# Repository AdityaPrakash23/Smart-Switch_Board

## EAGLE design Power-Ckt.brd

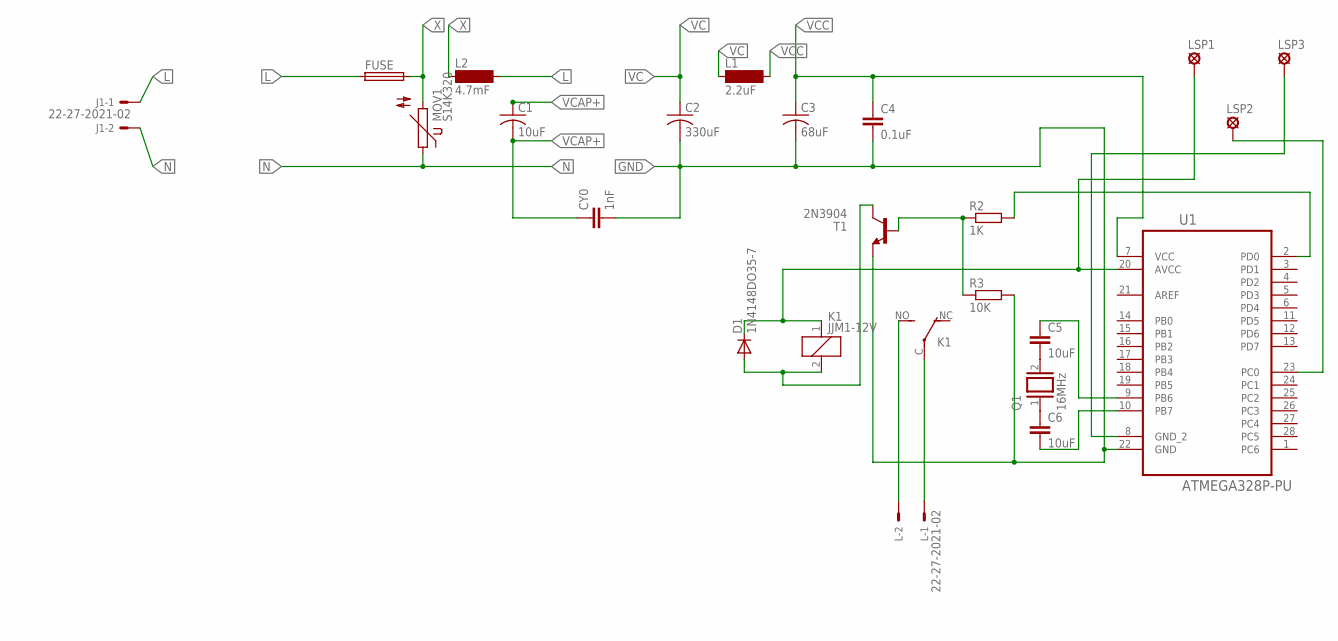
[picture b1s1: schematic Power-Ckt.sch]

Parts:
C1: 10uF; C0805K
C2: 330uF; C0805K
C3: 68uF; C0805K
C4: 0.1uF; C1808
C5, C6: 10uF; C2.5-3
CY0: 1nF; C1808
D1: 1N4148DO35-7; DO35-7
FUSE: GSH15
J1: 22-27-2021-02; 6410-02
K1: JJM1-12V; JJM1C
L: 22-27-2021-02; 6410-02
L1: 2.2uF; SM-1206
L2: 4.7mF; SM-1206
LSP1, LSP2, LSP3: LSP13
MOV1: S14K320
Q1: 16MHz; QS
R2: 1K; 0204/5
R3: 10K; 0204/5
T1: 2N3904; TO92
U1: ATMEGA328P-PU; DIP254P762X457-28

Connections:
GND: C2.2, C3.2, C4.2, CY0.2, R3.2, T1.3 (E), U1.22 (GND)
L: FUSE.1, J1.1, L2.2
N: J1.2, MOV1.1
unnamed: R2.2, U1.2 (PD0)
unnamed: C5.2, Q1.2
unnamed: C6.1, Q1.1
unnamed: C5.1, U1.9 (PB6)
unnamed: C6.2, U1.10 (PB7)
unnamed: LSP2.MP, U1.23 (PC0)
unnamed: D1.C, K1.1, LSP1.MP, U1.20 (AVCC)
unnamed: LSP3.MP, U1.8 (GND_2)
unnamed: K1.NO (S), L.2
unnamed: K1.C, L.1
unnamed: R2.1, R3.1, T1.2 (B)
unnamed: D1.A, K1.2, T1.1 (C)
VC: C2.1, L1.1
VCAP+: C1.1
VCAP-: C1.2, CY0.1
VCC: C3.1, C4.1, L1.2, U1.7 (VCC)
X: FUSE.2, L2.1, MOV1.2

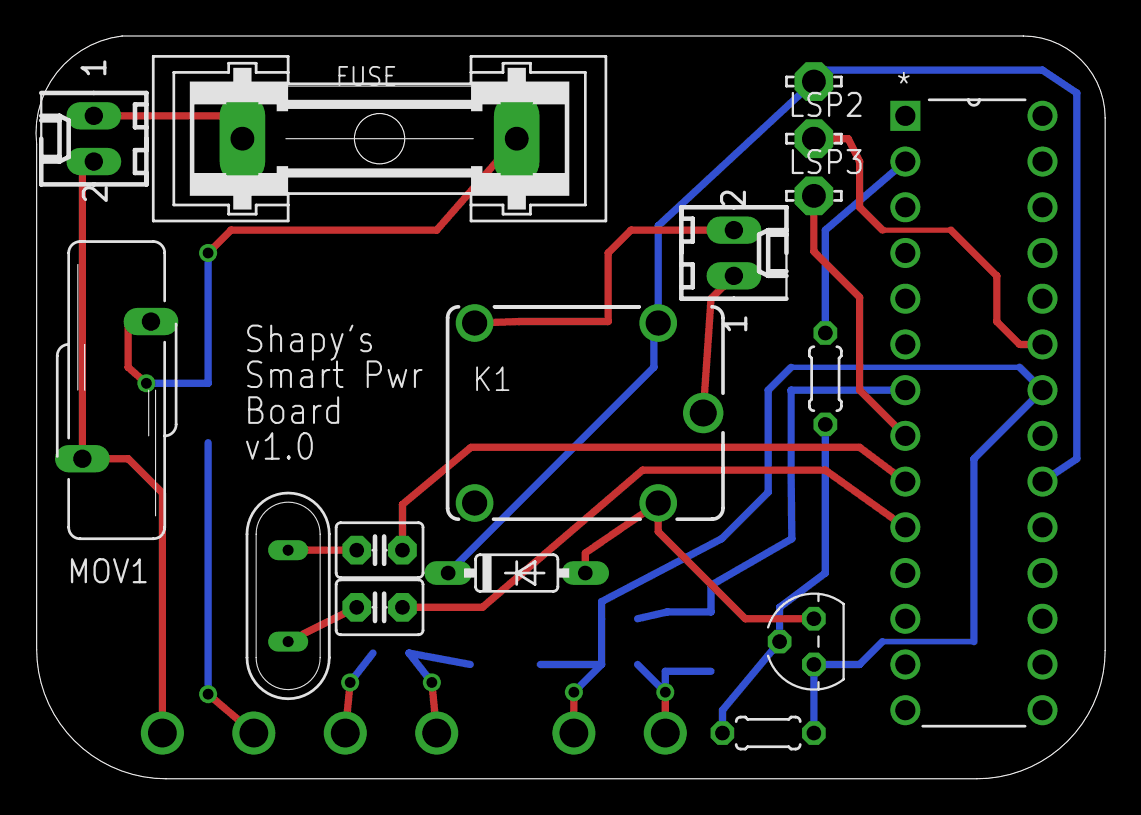
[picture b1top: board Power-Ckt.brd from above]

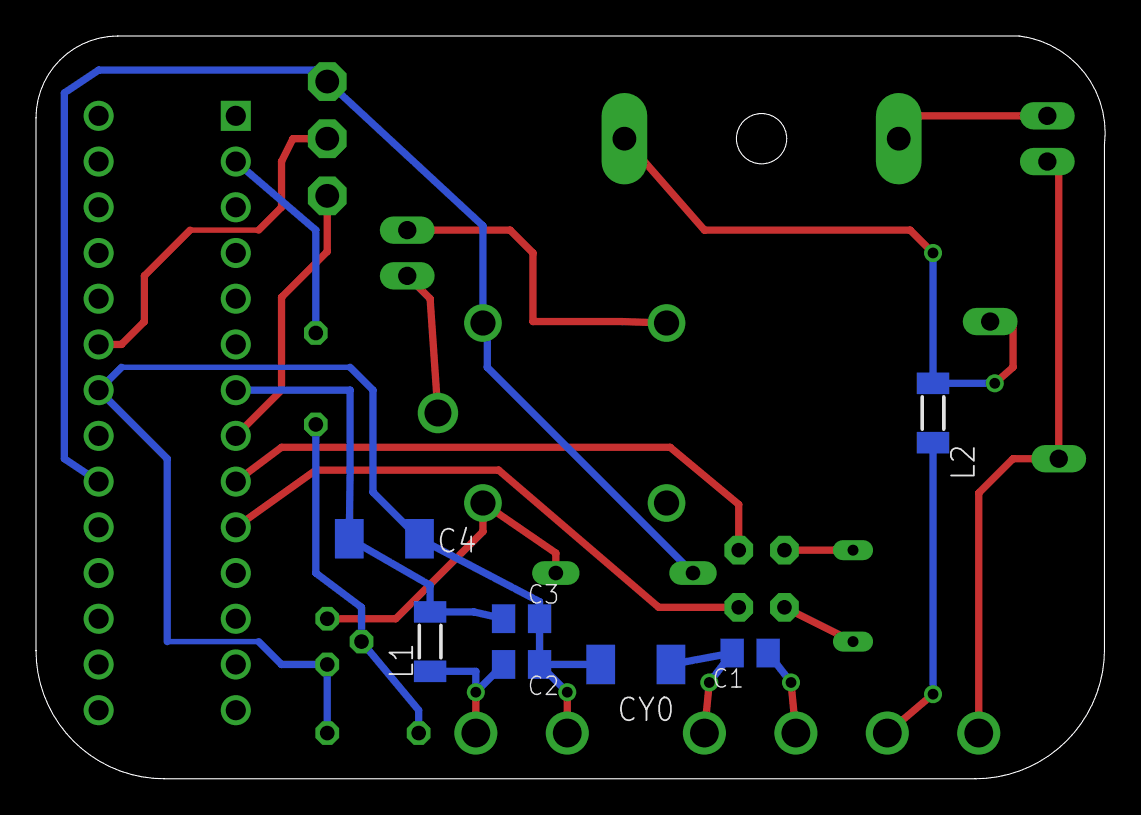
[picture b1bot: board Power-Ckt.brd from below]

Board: 2 copper layers, 59.4 x 41.3 mm, 23 parts (7 on the bottom side), 19 nets.

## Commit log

2017-06-14 These are the designs for the smart-power board
